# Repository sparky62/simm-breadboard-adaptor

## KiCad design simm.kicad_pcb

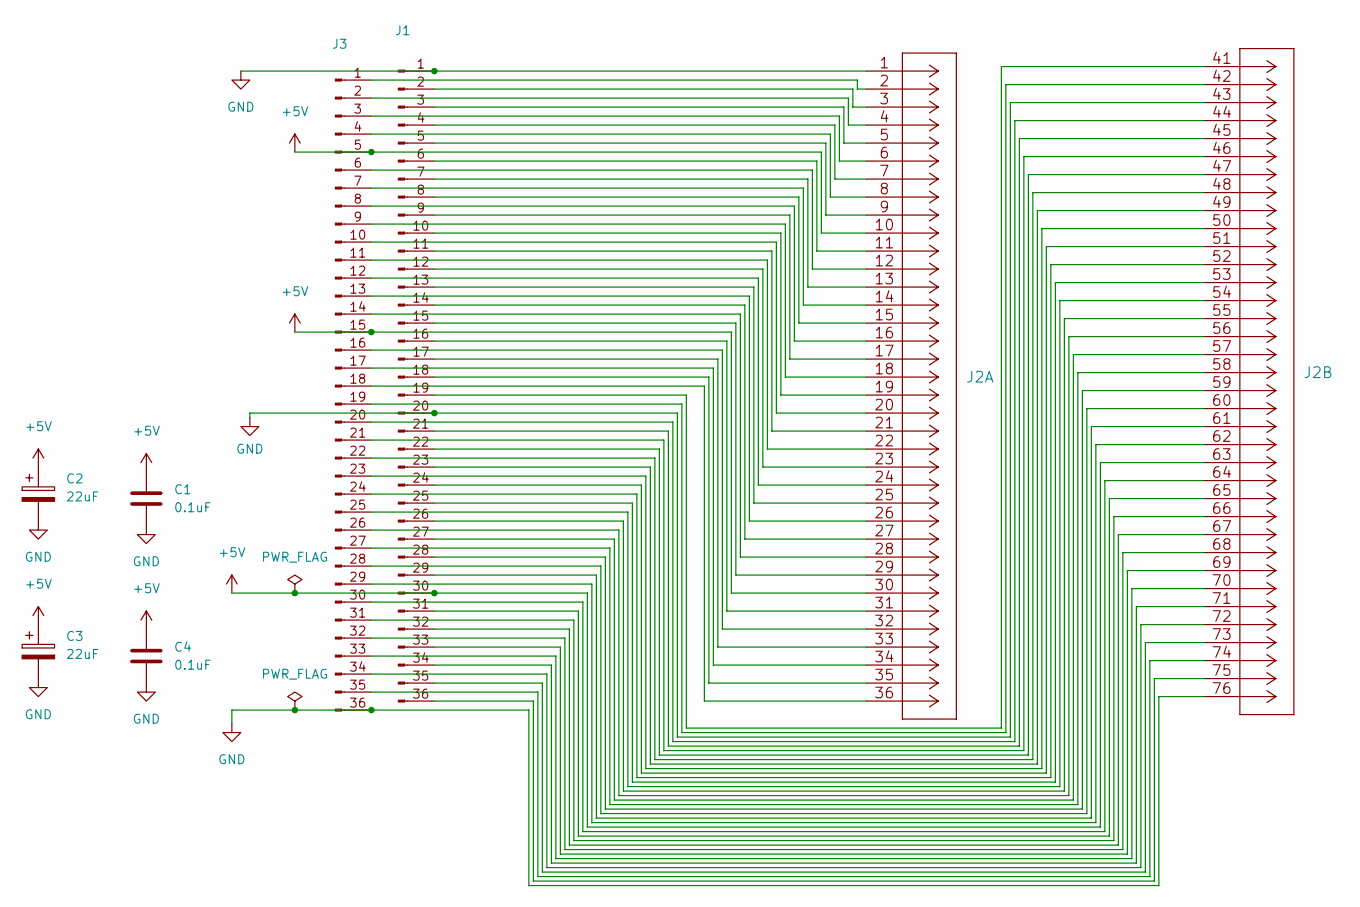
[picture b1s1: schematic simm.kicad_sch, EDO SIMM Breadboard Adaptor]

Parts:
C1, C4: 0.1uF; C_Disc_D4.3mm_W1.9mm_P5.00mm
C2, C3: 22uF; CP_Radial_D5.0mm_P2.00mm
J1, J3: Conn_01x36_Male; PinHeader_1x36_P2.54mm_Vertical
J2: 5822134-3

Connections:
+5V: C1.2, C2.1, C3.1, C4.2, J1.30, J2.10, J2.30, J2.63, J3.5, J3.15
GND: C1.1, C2.2, C3.2, C4.1, J1.1, J1.20, J2.1, J2.43, J2.76, J3.36
unnamed: J1.2, J2.3
unnamed: J1.3, J2.5
unnamed: J1.4, J2.7
unnamed: J1.5, J2.9
unnamed: J1.6, J2.11
unnamed: J1.7, J2.13
unnamed: J1.8, J2.15
unnamed: J1.9, J2.17
unnamed: J1.10, J2.19
unnamed: J1.11, J2.21
unnamed: J1.12, J2.23
unnamed: J1.13, J2.25
unnamed: J1.14, J2.27
unnamed: J1.15, J2.29
unnamed: J1.16, J2.31
unnamed: J1.17, J2.33
unnamed: J1.18, J2.35
unnamed: J1.19, J2.41
unnamed: J1.21, J2.45
unnamed: J1.22, J2.47
unnamed: J1.23, J2.49
unnamed: J1.24, J2.51
unnamed: J1.25, J2.53
unnamed: J1.26, J2.55
unnamed: J1.27, J2.57
unnamed: J1.28, J2.59
unnamed: J1.29, J2.61
unnamed: J1.31, J2.65
unnamed: J1.32, J2.67
unnamed: J1.33, J2.69
unnamed: J1.34, J2.71
unnamed: J1.35, J2.73
unnamed: J1.36, J2.75
unnamed: J2.2, J3.1
unnamed: J2.4, J3.2
unnamed: J2.6, J3.3
unnamed: J2.8, J3.4
unnamed: J2.12, J3.6
unnamed: J2.14, J3.7
unnamed: J2.16, J3.8
unnamed: J2.18, J3.9
unnamed: J2.20, J3.10
unnamed: J2.22, J3.11
unnamed: J2.24, J3.12
unnamed: J2.26, J3.13
unnamed: J2.28, J3.14
unnamed: J2.32, J3.16
unnamed: J2.34, J3.17
unnamed: J2.36, J3.18
unnamed: J2.42, J3.19
unnamed: J2.44, J3.20
unnamed: J2.46, J3.21
unnamed: J2.48, J3.22
unnamed: J2.50, J3.23
unnamed: J2.52, J3.24
unnamed: J2.54, J3.25
unnamed: J2.56, J3.26
unnamed: J2.58, J3.27
unnamed: J2.60, J3.28
unnamed: J2.62, J3.29
unnamed: J2.64, J3.30
unnamed: J2.66, J3.31
unnamed: J2.70, J3.33
unnamed: J2.72, J3.34
unnamed: J2.68, J3.32
unnamed: J2.74, J3.35

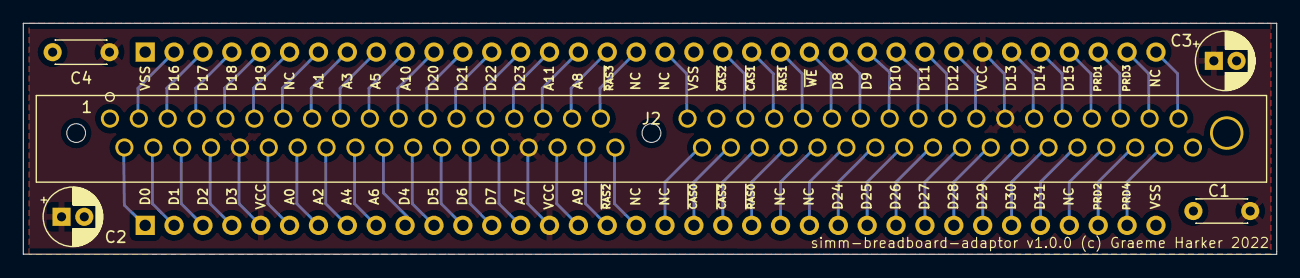
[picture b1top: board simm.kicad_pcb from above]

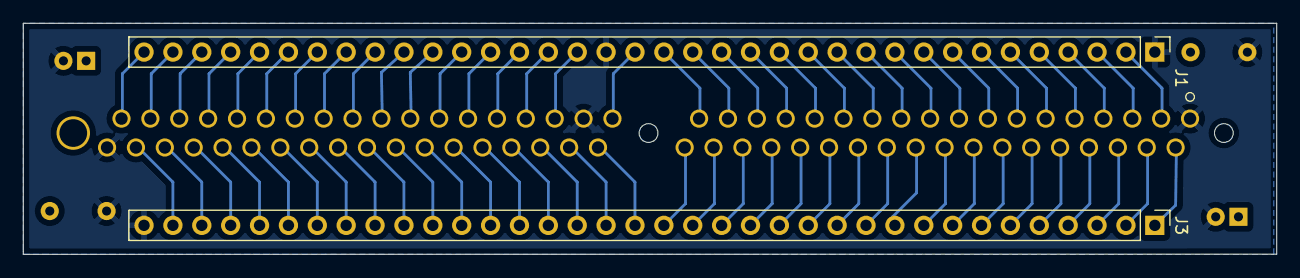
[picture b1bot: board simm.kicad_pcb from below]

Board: 2 copper layers, 110.2 x 20.3 mm, 7 parts (2 on the bottom side), 68 nets.

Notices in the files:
parts and their libraries:
Copyright 2021 Accelerated Designs. All rights reserved.
